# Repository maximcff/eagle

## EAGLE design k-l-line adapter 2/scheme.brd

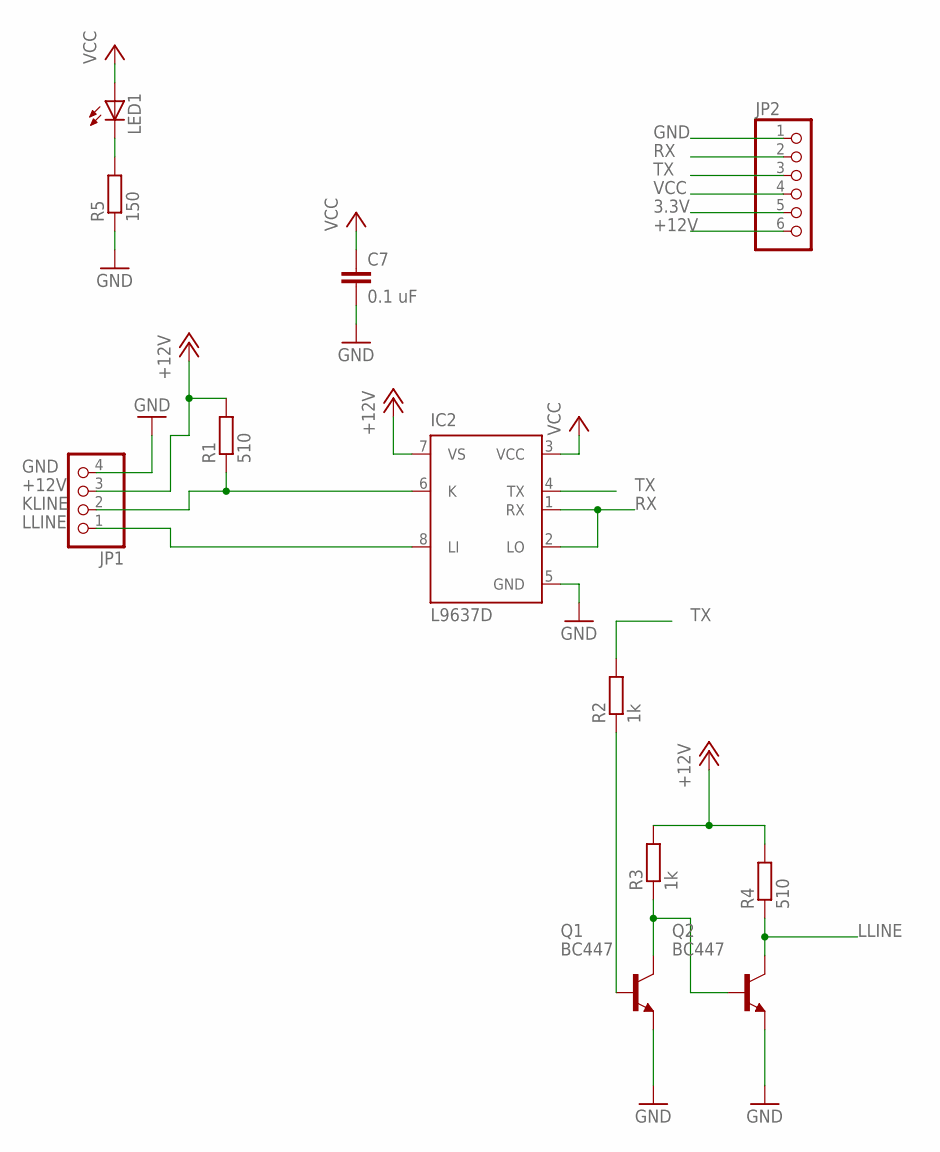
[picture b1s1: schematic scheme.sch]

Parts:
C7: 0.1 uF; C0805K
IC2: L9637D; SO08
JP1: PINHD-1X4; 1X04
JP2: PINHD-1X6; 1X06
LED1: LEDSML1206; SML1206
Q1, Q2: BC447; TO92-EBC
R1, R4: 510; R0805
R2, R3: 1k; R0805
R5: 150; R0805

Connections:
3.3V: JP2.5
+12V: IC2.7 (VS), JP1.3, JP2.6, R1.2, R3.2, R4.2
GND: C7.2, IC2.5 (GND), JP1.4, JP2.1, Q1.E, Q2.E, R5.1
KLINE: IC2.6 (K), JP1.2, R1.1
LLINE: IC2.8 (LI), JP1.1, Q2.C, R4.1
unnamed: LED1.C, R5.2
unnamed: Q1.B, R2.1
unnamed: Q1.C, Q2.B, R3.1
RX: IC2.1 (RX), IC2.2 (LO), JP2.2
TX: IC2.4 (TX), JP2.3, R2.2
VCC: C7.1, IC2.3 (VCC), JP2.4, LED1.A

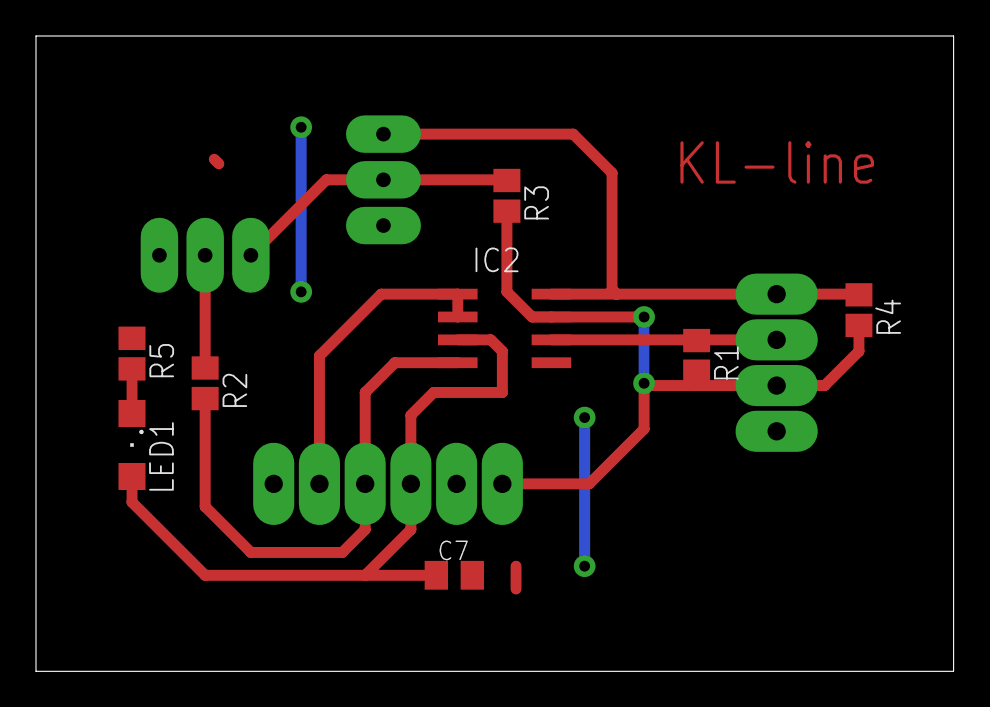
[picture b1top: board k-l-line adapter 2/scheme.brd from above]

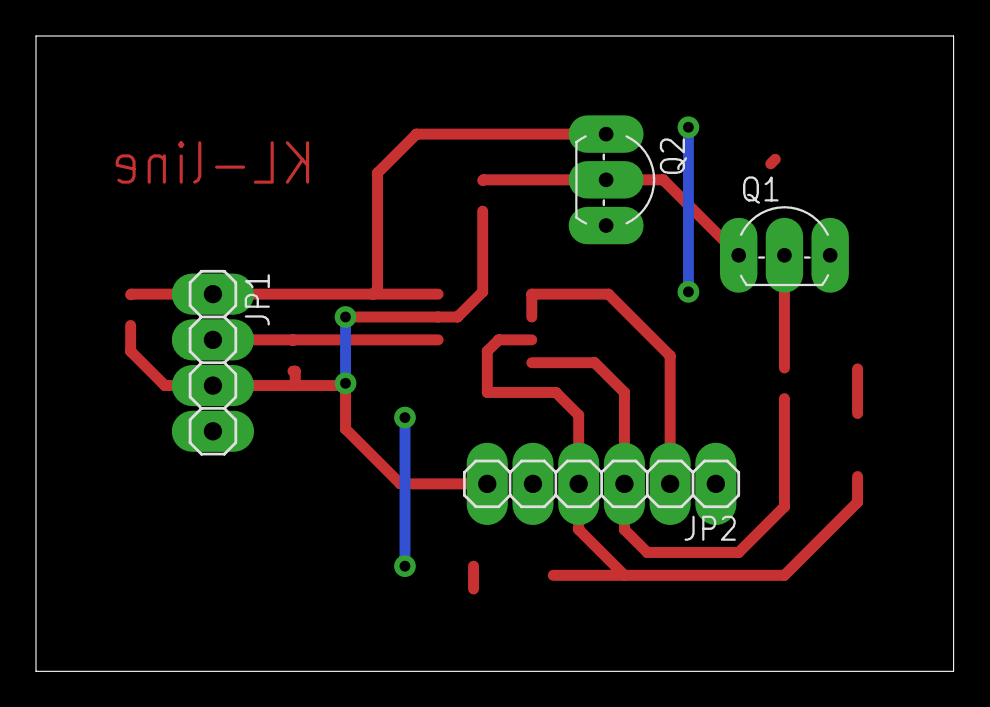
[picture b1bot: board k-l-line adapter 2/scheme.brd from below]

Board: 2 copper layers, 51.0 x 35.3 mm, 12 parts (4 on the bottom side), 10 nets.

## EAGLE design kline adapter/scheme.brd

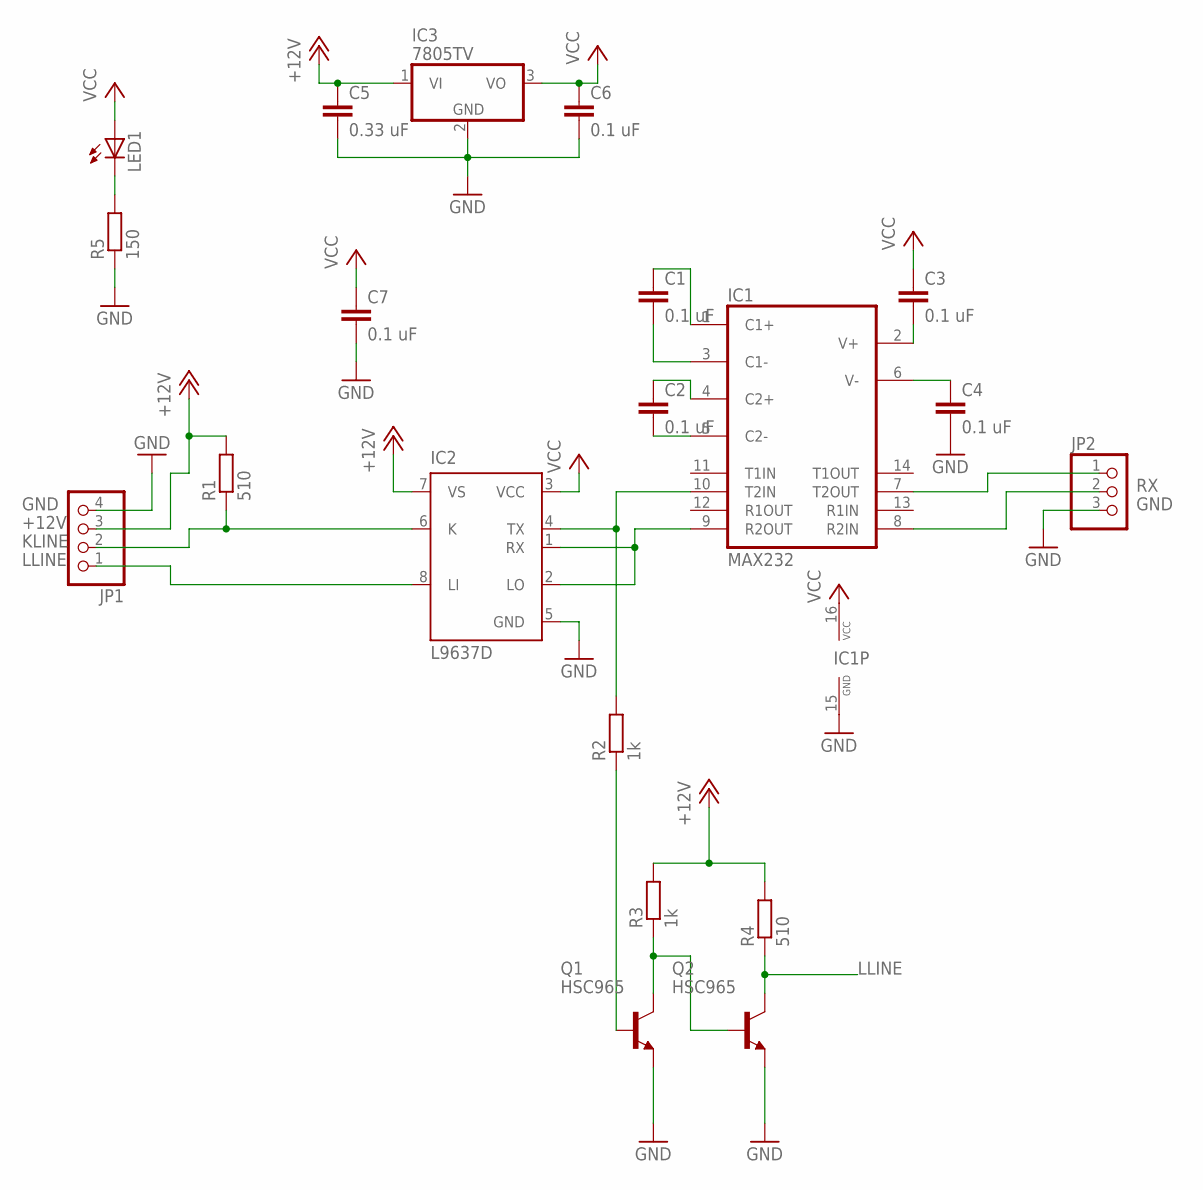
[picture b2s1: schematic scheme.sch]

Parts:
C1, C2, C3, C4, C6, C7: 0.1 uF; C0805K
C5: 0.33 uF; C0805K
IC1: MAX232; DIL16
IC2: L9637D; SO08
IC3: 7805TV; TO220V
JP1: PINHD-1X4; 1X04
JP2: PINHD-1X3; 1X03
LED1: LED3MM
Q1, Q2: HSC965; TO92-
R1, R4: 510; R0805
R2, R3: 1k; R0805
R5: 150; R0805

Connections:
+12V: C5.1, IC2.7 (VS), IC3.1 (VI), JP1.3, R1.2, R3.2, R4.2
GND: C4.2, C5.2, C6.2, C7.2, IC1.15 (GND), IC2.5 (GND), IC3.2 (GND), JP1.4, JP2.3, Q1.3 (E), Q2.3 (E), R5.1
KLINE: IC2.6 (K), JP1.2, R1.1
LLINE: IC2.8 (LI), JP1.1, Q2.2 (C), R4.1
unnamed: IC1.10 (T2IN), IC2.4 (TX), R2.2
unnamed: IC1.9 (R2OUT), IC2.1 (RX), IC2.2 (LO)
unnamed: C2.2, IC1.5 (C2-)
unnamed: C2.1, IC1.4 (C2+)
unnamed: C1.2, IC1.3 (C1-)
unnamed: C1.1, IC1.1 (C1+)
unnamed: C3.2, IC1.2 (V+)
unnamed: C4.1, IC1.6 (V-)
unnamed: IC1.7 (T2OUT), JP2.1
unnamed: LED1.K (C), R5.2
unnamed: Q1.1 (B), R2.1
unnamed: Q1.2 (C), Q2.1 (B), R3.1
RX: IC1.8 (R2IN), JP2.2
VCC: C3.1, C6.1, C7.1, IC1.16 (VCC), IC2.3 (VCC), IC3.3 (VO), LED1.A

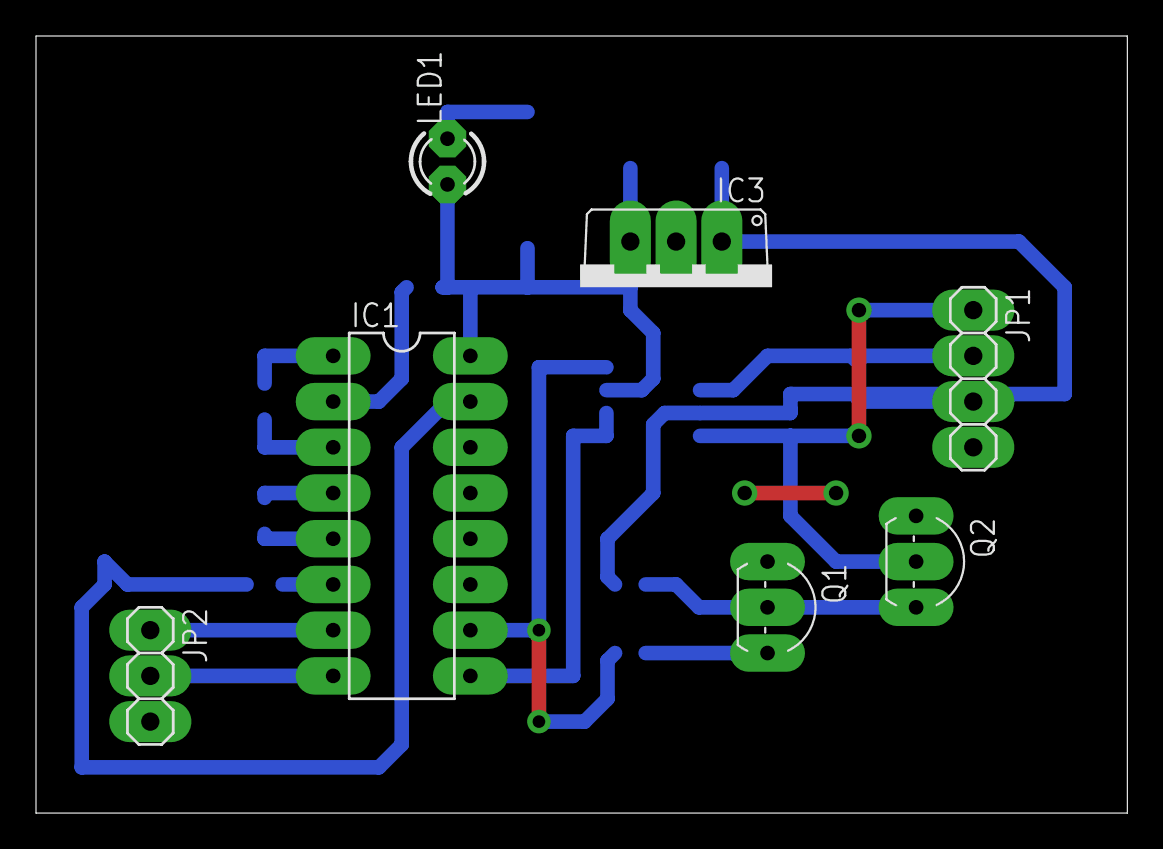
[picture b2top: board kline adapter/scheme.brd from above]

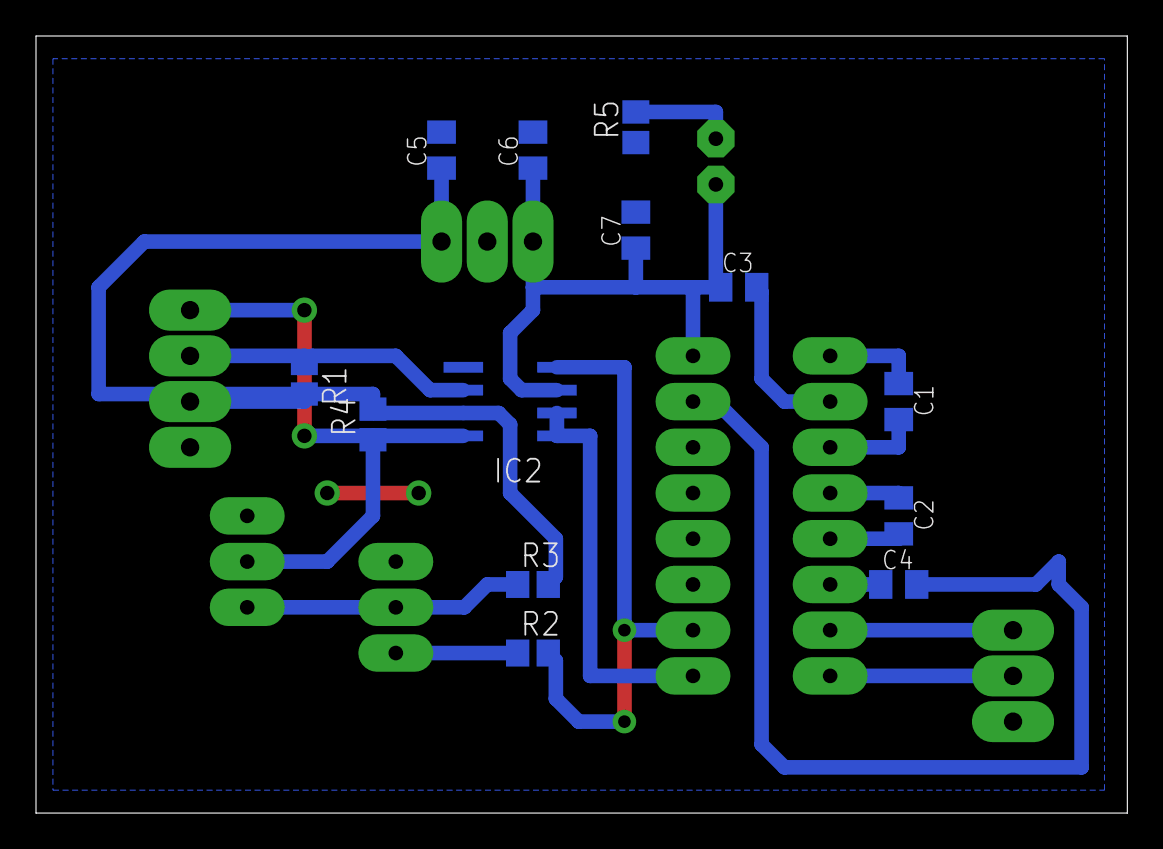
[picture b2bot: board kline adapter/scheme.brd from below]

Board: 2 copper layers, 60.6 x 43.2 mm, 20 parts (13 on the bottom side), 18 nets.

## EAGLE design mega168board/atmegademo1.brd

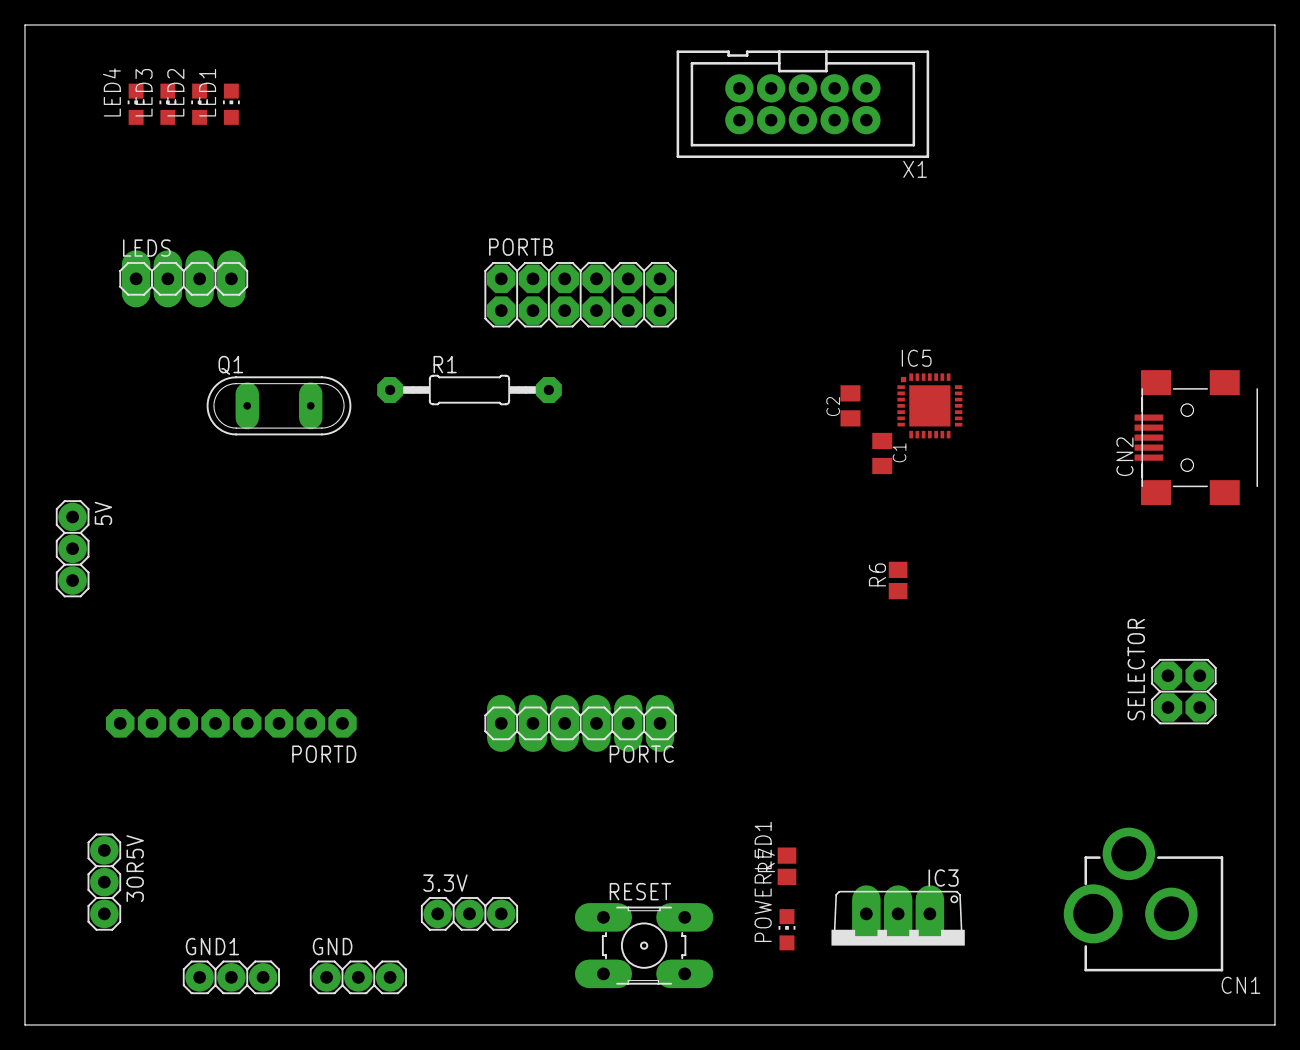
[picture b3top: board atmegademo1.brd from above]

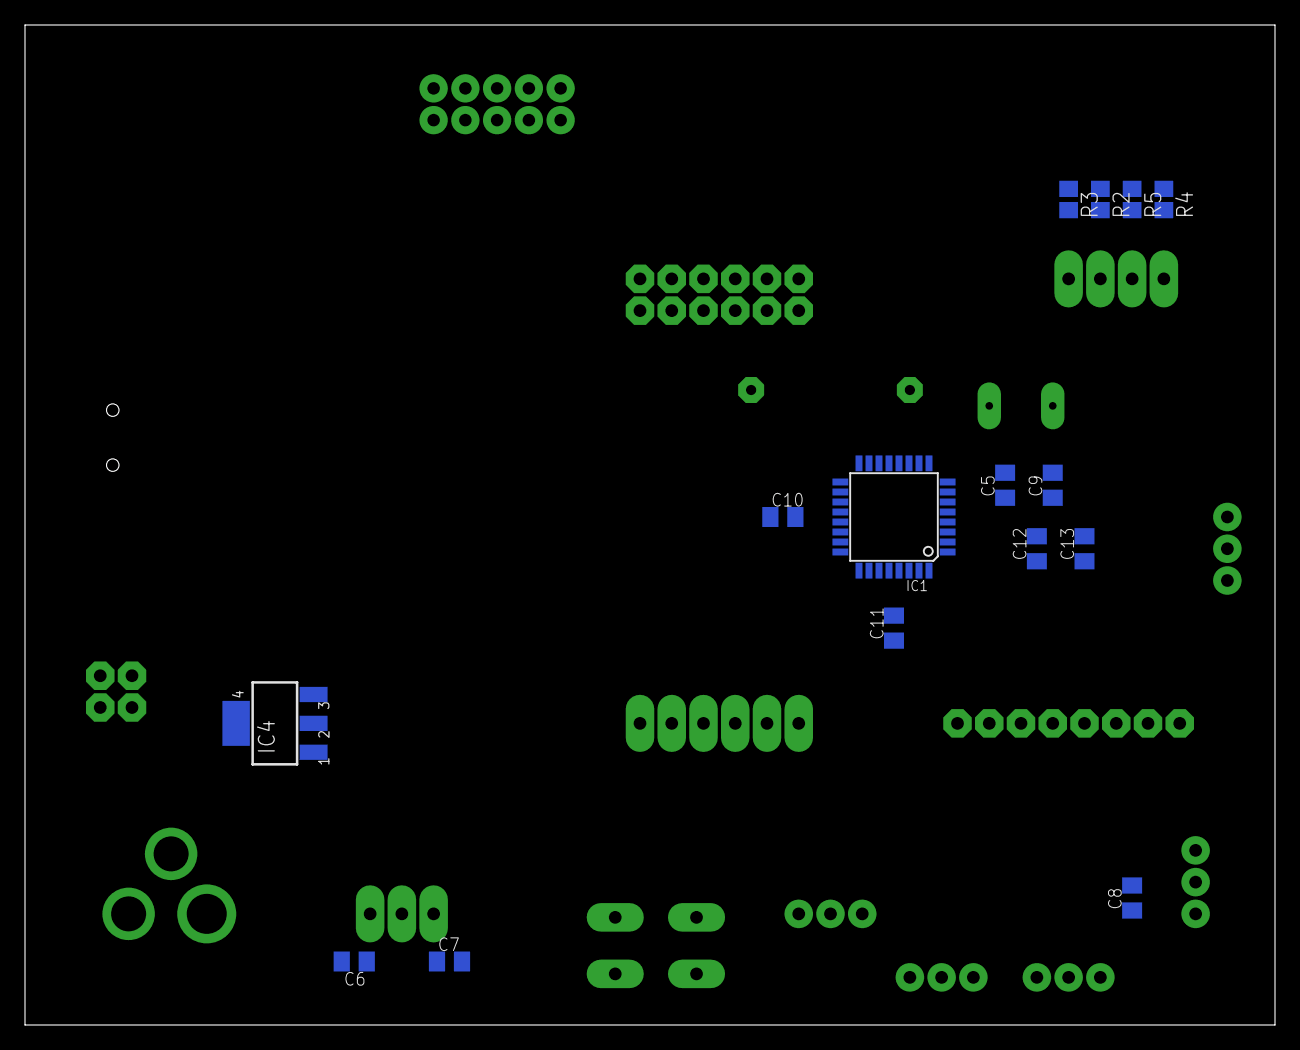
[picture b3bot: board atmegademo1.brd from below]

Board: 2 copper layers, 100.0 x 80.0 mm, 42 parts (15 on the bottom side), 44 nets, no tracks yet.

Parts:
3.3V, 3OR5V, 5V: 1X03
C1: 1 uF; C0805K
C2: 0.1 uF; C0805K
C5, C9: 22pf; C0805K
C6: 0.33uF; C0805K
C7, C8: 0.1uF; C0805K
C10, C13: 100n; C0805K
C11: 100 uF; C0805K
C12: 47uF; C0805K
CN1: DCJACK_2MM_PTH
CN2: USB-MINIB
GND, GND1: 1X03
IC1: MEGA8-AI; TQFP32-08
IC3: 7805TV; TO220V
IC4: 317EMP; SOT223
IC5: CP2102; MLP28
LED1, LED2, LED3, LED4: CHIP-LED0805
LEDS: 1X04
PORTB: 2X06
PORTC: 1X06
PORTD: 1X08-CLEANBIG
POWERLED1: CHIP-LED0805
Q1: QS
R1: 10k; 0207/12
R2, R3, R4, R5, R7: R0805
R6: 4.7k; R0805
RESET: B3F-10XX
SELECTOR: 2X02
X1: 2510-; PAK100/2500-10

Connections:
+3V3: 3.3V.1, 3.3V.2, 3.3V.3, 3OR5V.3, C8.1, IC4.2, R6.1
+5V: 3OR5V.1, 5V.1, 5V.2, 5V.3, IC4.3, POWERLED1.A, SELECTOR.2, SELECTOR.4
D+: CN2.D+, IC5.4
D-: CN2.D-, IC5.5
GND: C1.2, C2.2, C5.1, C6.2, C7.2, C8.2, C9.1, C10.1, C11.1, C12.1, C13.1, CN1.GND, CN1.GNDBREAK, CN2.GND, GND.1, GND.2, GND.3, GND1.1, GND1.2, GND1.3, IC1.3, IC1.5, IC1.21, IC3.2, IC4.1, IC5.3, IC5.EXP, IC5.M, LED1.C, LED2.C, LED3.C, LED4.C, R7.2, RESET.3, RESET.4, X1.1, X1.3
MISO: IC1.16, PORTB.9, PORTB.10, X1.2
MOSI: IC1.15, PORTB.7, PORTB.8, X1.10
unnamed: POWERLED1.C, R7.1
unnamed: C2.1, IC5.6
unnamed: IC5.9, R6.2
unnamed: LEDS.4, R3.2
unnamed: LEDS.3, R2.2
unnamed: IC1.32, PORTD.3
unnamed: IC1.1, PORTD.4
unnamed: IC1.2, PORTD.5
unnamed: C6.1, CN1.PWR, IC3.1
unnamed: IC1.9, PORTD.6
unnamed: IC1.23, PORTC.1
unnamed: IC1.10, PORTD.7
unnamed: IC1.11, PORTD.8
unnamed: IC1.24, PORTC.2
unnamed: IC1.25, PORTC.3
unnamed: IC1.26, PORTC.4
unnamed: LEDS.2, R5.2
unnamed: LED1.A, R3.1
unnamed: LED2.A, R2.1
unnamed: C10.2, IC1.20
unnamed: C5.2, IC1.7, Q1.2
unnamed: LED4.A, R4.1
unnamed: LED3.A, R5.1
unnamed: C9.2, IC1.8, Q1.1
unnamed: IC1.13, PORTB.3, PORTB.4
unnamed: IC1.14, PORTB.5, PORTB.6
unnamed: IC1.12, PORTB.1, PORTB.2
unnamed: LEDS.1, R4.2
REGOUT: C7.1, IC3.3, SELECTOR.1
RESET: C11.2, IC1.29, R1.2, RESET.1, RESET.2, X1.6
RX: IC1.30, IC5.26, PORTD.1
SCK: IC1.17, PORTB.11, PORTB.12, X1.4
SCL: IC1.28, PORTC.6
SDA: IC1.27, PORTC.5
TX: IC1.31, IC5.25, PORTD.2
USBVCC: CN2.VBUS, IC5.8, SELECTOR.3
VCC: 3OR5V.2, C1.1, C12.2, C13.2, IC1.4, IC1.6, IC1.18, IC5.7, R1.1

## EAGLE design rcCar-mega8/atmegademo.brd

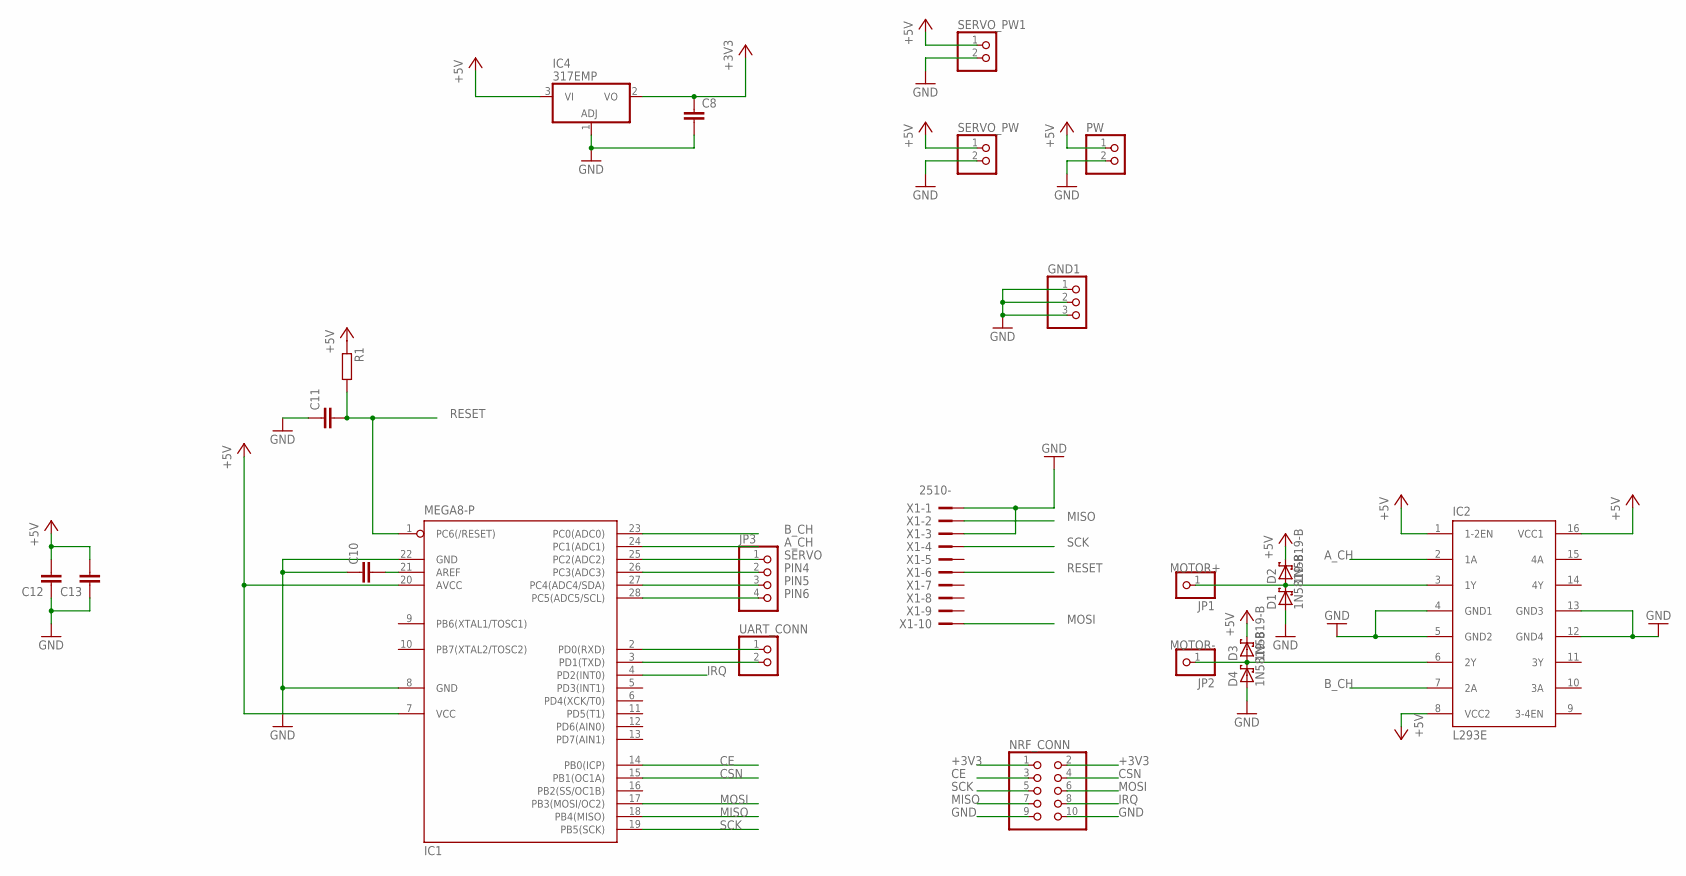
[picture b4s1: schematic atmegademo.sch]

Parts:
C8, C10, C11, C12, C13: C-EUC0805K; C0805K
D1, D2, D3, D4: 1N5819-B; DO41-7.6
GND1: PINHD-1X3; 1X03
IC1: MEGA8-P; DIL28-3
IC2: L293E; DIL16
IC4: 317EMP; SOT223
JP1, JP2: PINHD-1X1; 1X01
JP3: PINHD-1X4; 1X04
NRF_CONN: PINHD-2X5; 2X05
PW: PINHD-1X2; 1X02
R1: R-EU_0207/10; 0207/10
SERVO_PW, SERVO_PW1: PINHD-1X2; 1X02
UART_CONN: PINHD-1X2; 1X02
X1: 2510-; PAK100/2500-10

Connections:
+3V3: C8.1, IC4.2 (VO), NRF_CONN.1, NRF_CONN.2
+5V: C12.2, C13.2, D2.C, D3.C, IC1.7 (VCC), IC1.20 (AVCC), IC2.1 (1-2EN), IC2.8 (VCC2), IC2.16 (VCC1), IC4.3 (VI), PW.1, R1.1, SERVO_PW.1, SERVO_PW1.1
A_CH: IC1.24 (PC1(ADC1)), IC2.2 (1A)
B_CH: IC1.23 (PC0(ADC0)), IC2.7 (2A)
CE: IC1.14 (PB0(ICP)), NRF_CONN.3
CSN: IC1.15 (PB1(OC1A)), NRF_CONN.4
GND: C8.2, C10.1, C11.1, C12.1, C13.1, D1.A, D4.A, GND1.1, GND1.2, GND1.3, IC1.8 (GND), IC1.22 (GND), IC2.4 (GND1), IC2.5 (GND2), IC2.12 (GND4), IC2.13 (GND3), IC4.1 (ADJ), NRF_CONN.9, NRF_CONN.10, PW.2, SERVO_PW.2, SERVO_PW1.2, X1.1, X1.3
IRQ: IC1.4 (PD2(INT0)), NRF_CONN.8
MISO: IC1.18 (PB4(MISO)), NRF_CONN.7, X1.2
MOSI: IC1.17 (PB3(MOSI/OC2)), NRF_CONN.6, X1.10
MOTOR+: D1.C, D2.A, IC2.3 (1Y), JP1.1
MOTOR-: D3.A, D4.C, IC2.6 (2Y), JP2.1
unnamed: IC1.2 (PD0(RXD)), UART_CONN.1
unnamed: IC1.3 (PD1(TXD)), UART_CONN.2
unnamed: C10.2, IC1.21 (AREF)
PIN4: IC1.26 (PC3(ADC3)), JP3.2
PIN5: IC1.27 (PC4(ADC4/SDA)), JP3.3
PIN6: IC1.28 (PC5(ADC5/SCL)), JP3.4
RESET: C11.2, IC1.1 (PC6(/RESET)), R1.2, X1.6
SCK: IC1.19 (PB5(SCK)), NRF_CONN.5, X1.4
SERVO: IC1.25 (PC2(ADC2)), JP3.1

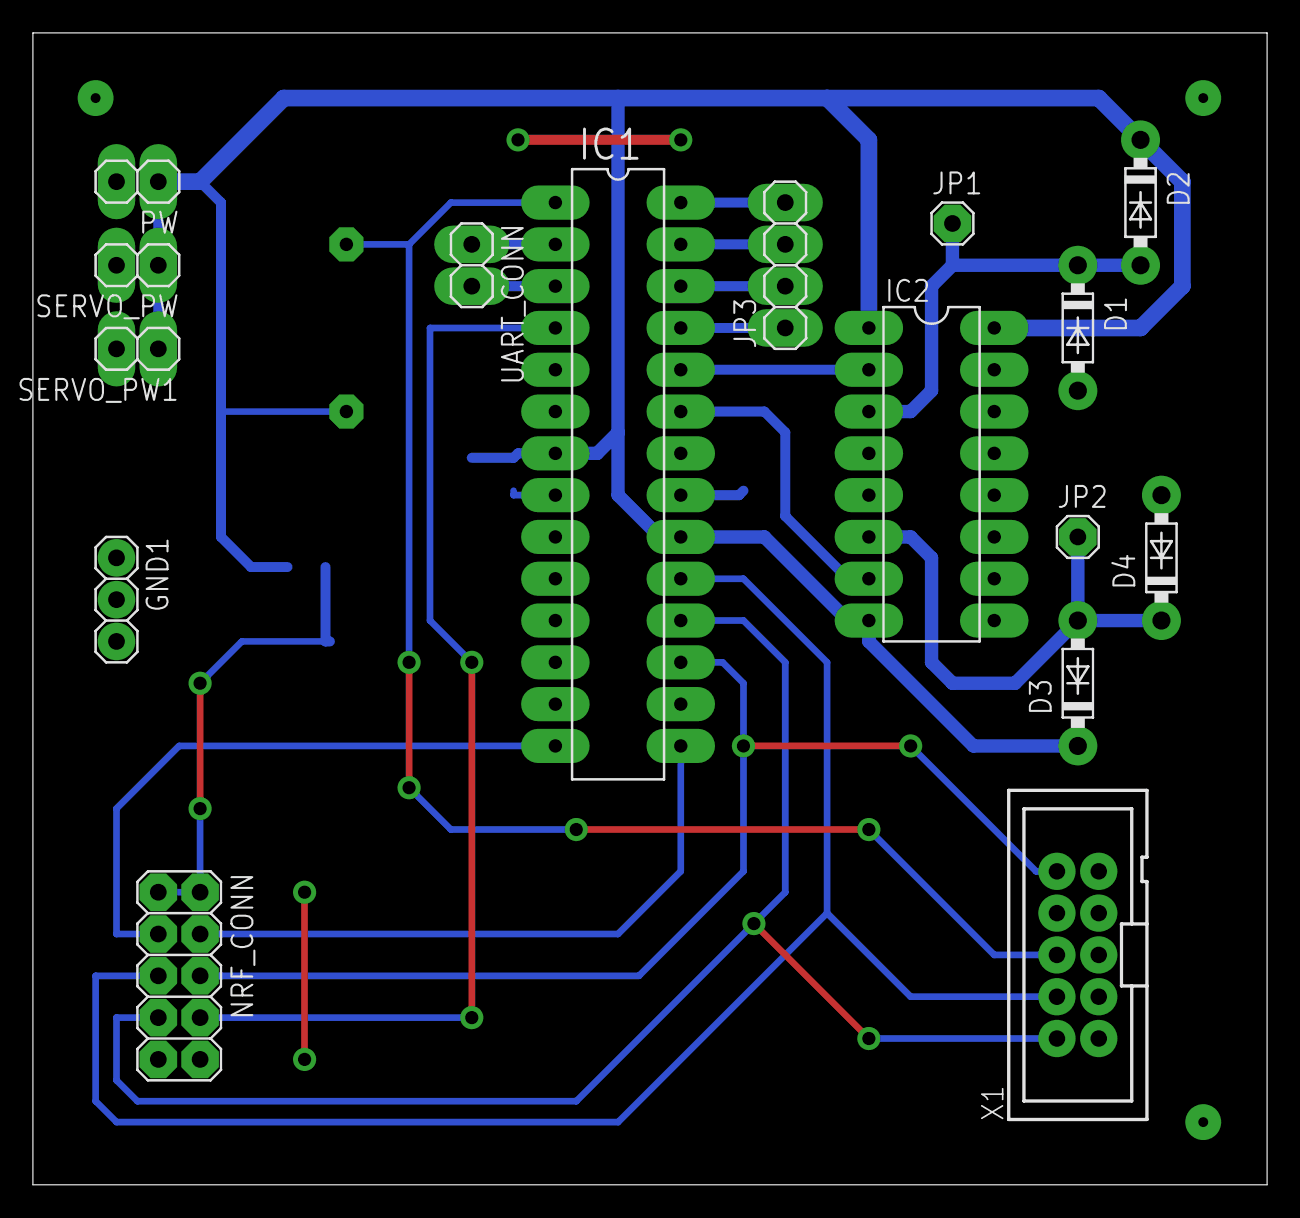
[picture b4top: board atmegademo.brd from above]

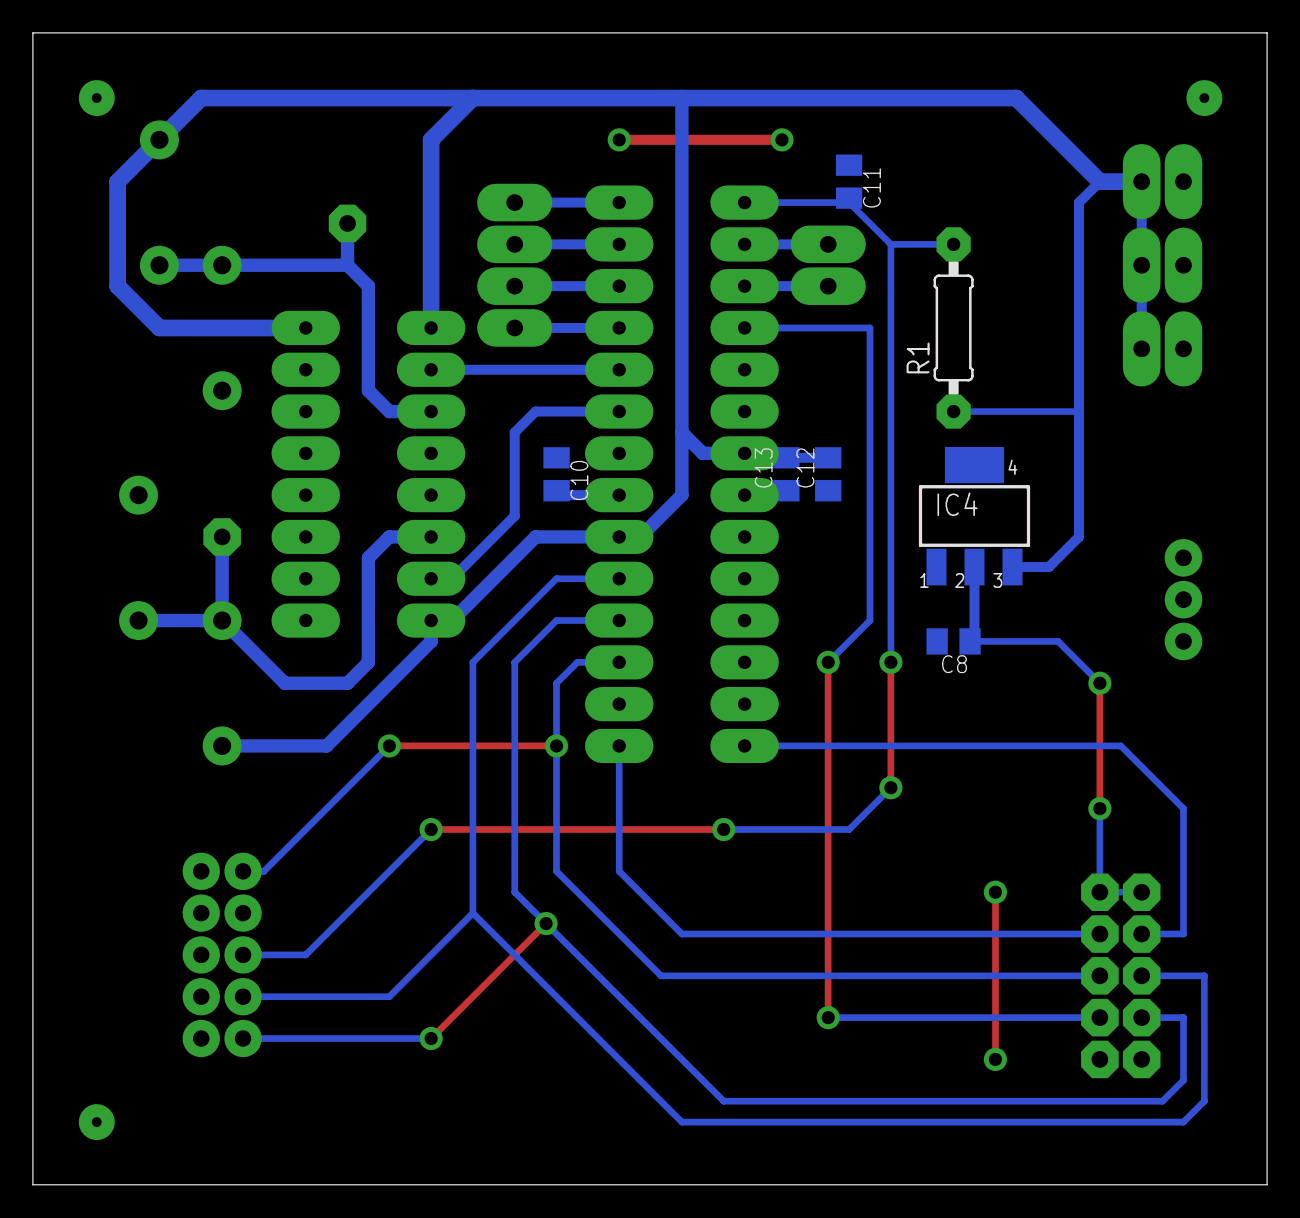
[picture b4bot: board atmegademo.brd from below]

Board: 2 copper layers, 75.0 x 70.0 mm, 23 parts (7 on the bottom side), 21 nets.

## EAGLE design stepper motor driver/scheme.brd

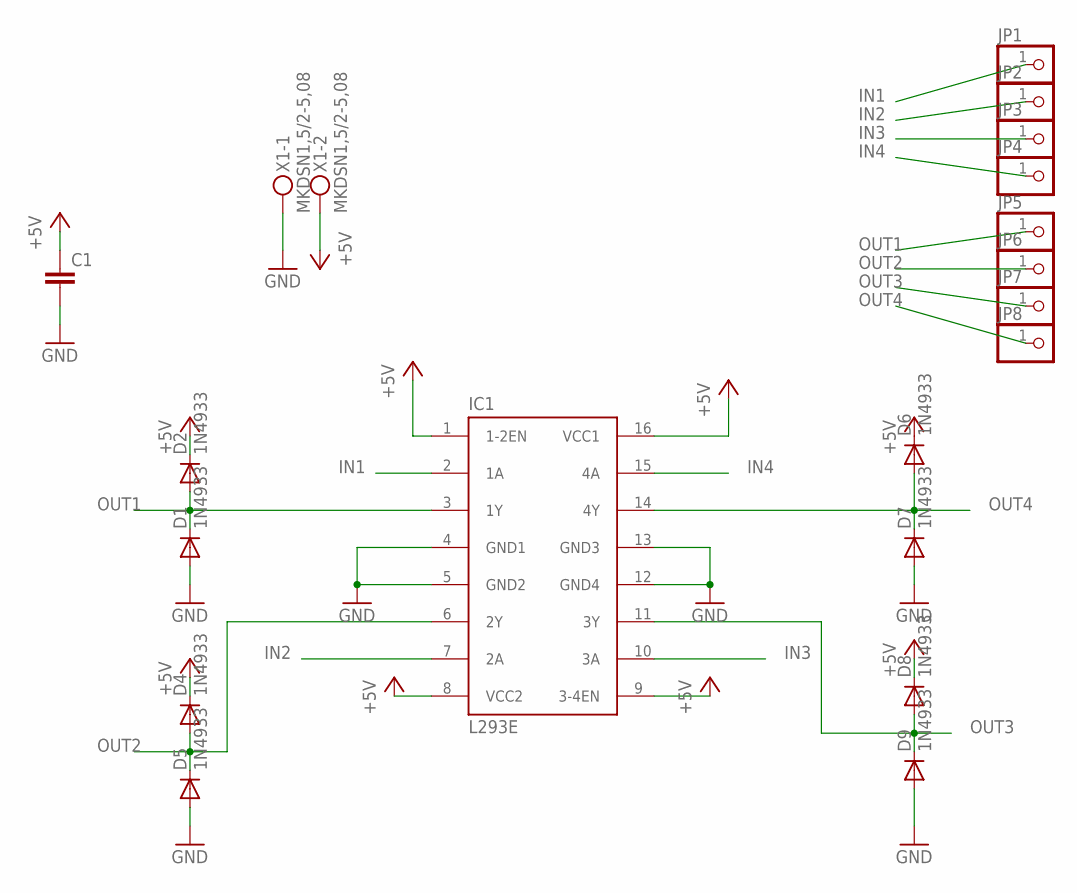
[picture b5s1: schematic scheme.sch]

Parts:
C1: C-EUC0805K; C0805K
D1, D2, D4, D5, D6, D7, D8, D9: 1N4933; DO41-10
IC1: L293E; DIL16
JP1, JP2, JP3, JP4, JP5, JP6, JP7, JP8: PINHD-1X1; 1X01
X1: MKDSN1,5/2-5,08

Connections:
+5V: C1.1, D2.C, D4.C, D6.C, D8.C, IC1.1 (1-2EN), IC1.8 (VCC2), IC1.9 (3-4EN), IC1.16 (VCC1), X1.2
GND: C1.2, D1.A, D5.A, D7.A, D9.A, IC1.4 (GND1), IC1.5 (GND2), IC1.12 (GND4), IC1.13 (GND3), X1.1
IN1: IC1.2 (1A), JP1.1
IN2: IC1.7 (2A), JP2.1
IN3: IC1.10 (3A), JP3.1
IN4: IC1.15 (4A), JP4.1
OUT1: D1.C, D2.A, IC1.3 (1Y), JP5.1
OUT2: D4.A, D5.C, IC1.6 (2Y), JP6.1
OUT3: D8.A, D9.C, IC1.11 (3Y), JP7.1
OUT4: D6.A, D7.C, IC1.14 (4Y), JP8.1

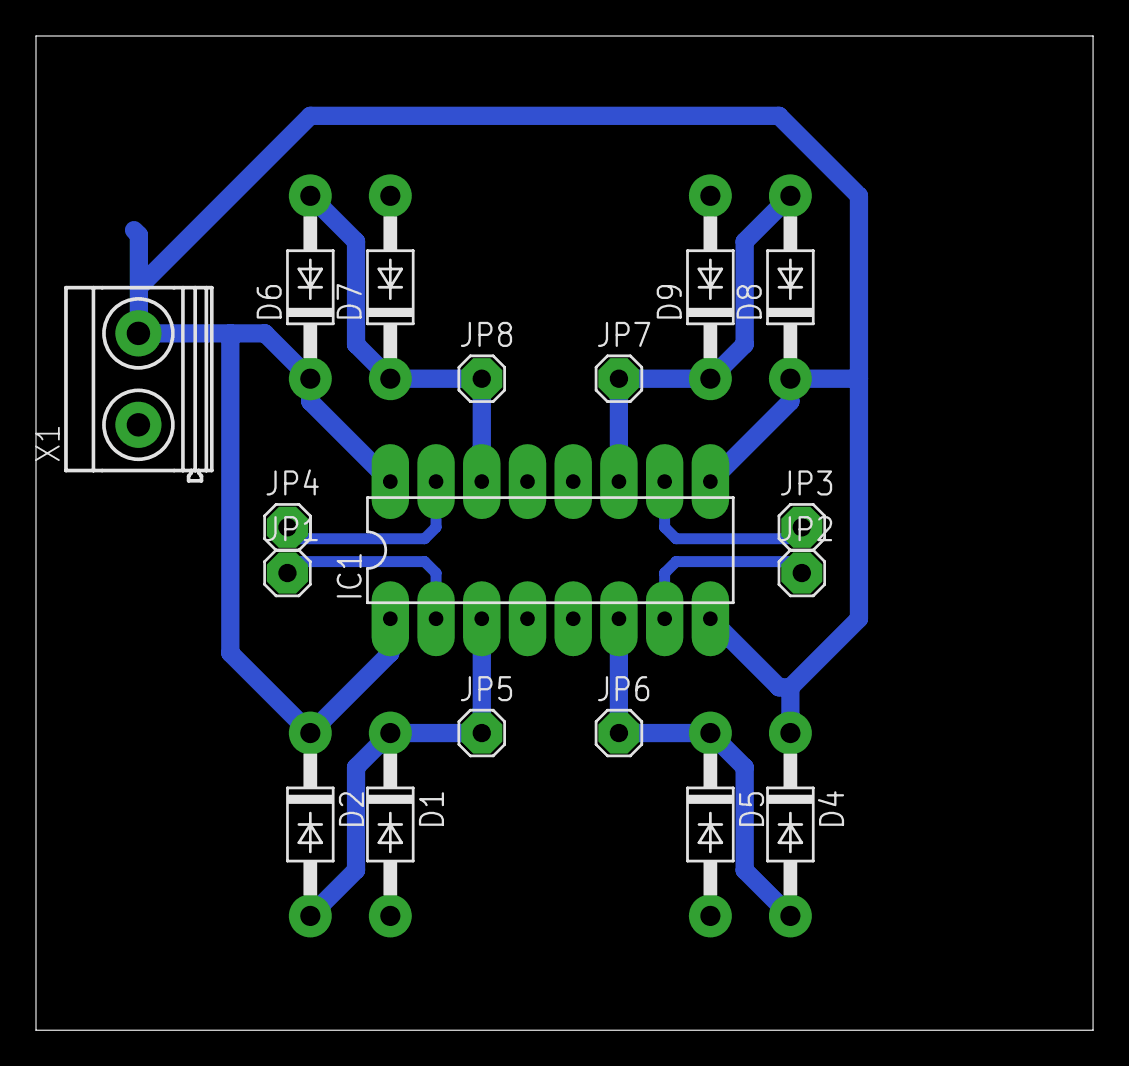
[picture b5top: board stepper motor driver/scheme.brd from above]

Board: 2 copper layers, 58.7 x 55.2 mm, 19 parts (1 on the bottom side), 10 nets.
